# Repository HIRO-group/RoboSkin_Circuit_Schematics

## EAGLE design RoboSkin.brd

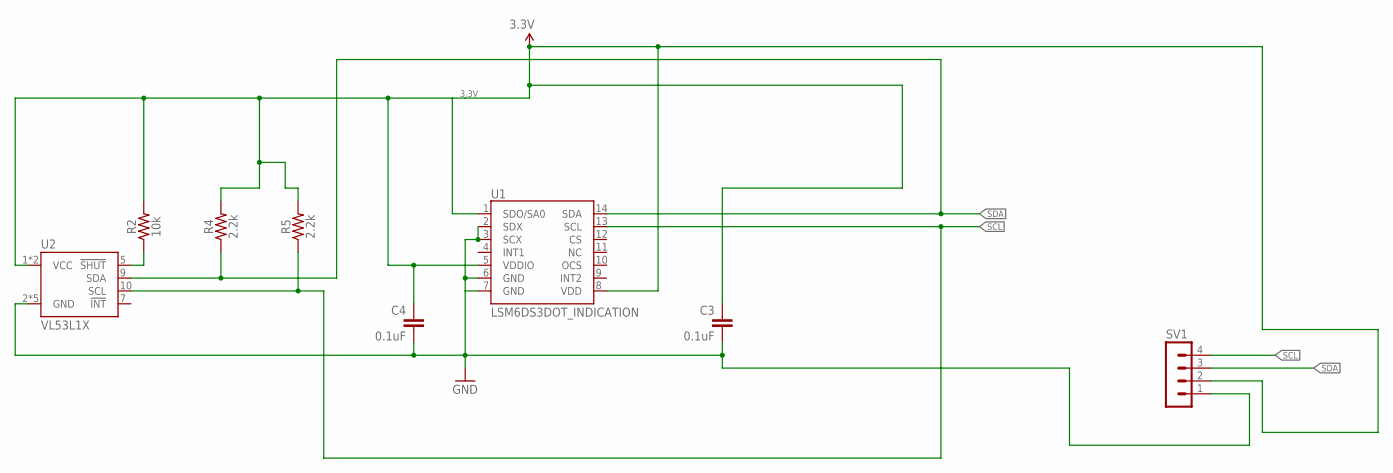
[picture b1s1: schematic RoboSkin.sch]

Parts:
C3, C4: 0.1uF; 0603-CAP
R2: 10k; 0603
R4, R5: 2.2k; 0603
SV1: MA04-1
U1: LSM6DS3DOT_INDICATION; LGA14L_DOT_INDICATOR
U2: VL53L1X

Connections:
3.3V: C3.1, C4.1, R2.2, R4.2, R5.2, SV1.2, U1.1 (SDO/SA0), U1.5 (VDDIO), U1.8 (VDD), U2.1 (VCC), U2.11 (VCC)
!SHUT: R2.1, U2.5 (!SHUT)
GND: C3.2, C4.2, SV1.1, U1.2 (SDX), U1.3 (SCX), U1.6 (GND), U1.7 (GND), U2.2 (GND), U2.3 (GND), U2.4 (GND), U2.6 (GND), U2.12 (GND)
SCL: R5.1, SV1.4, U1.13 (SCL), U2.10 (SCL)
SDA: R4.1, SV1.3, U1.14 (SDA), U2.9 (SDA)

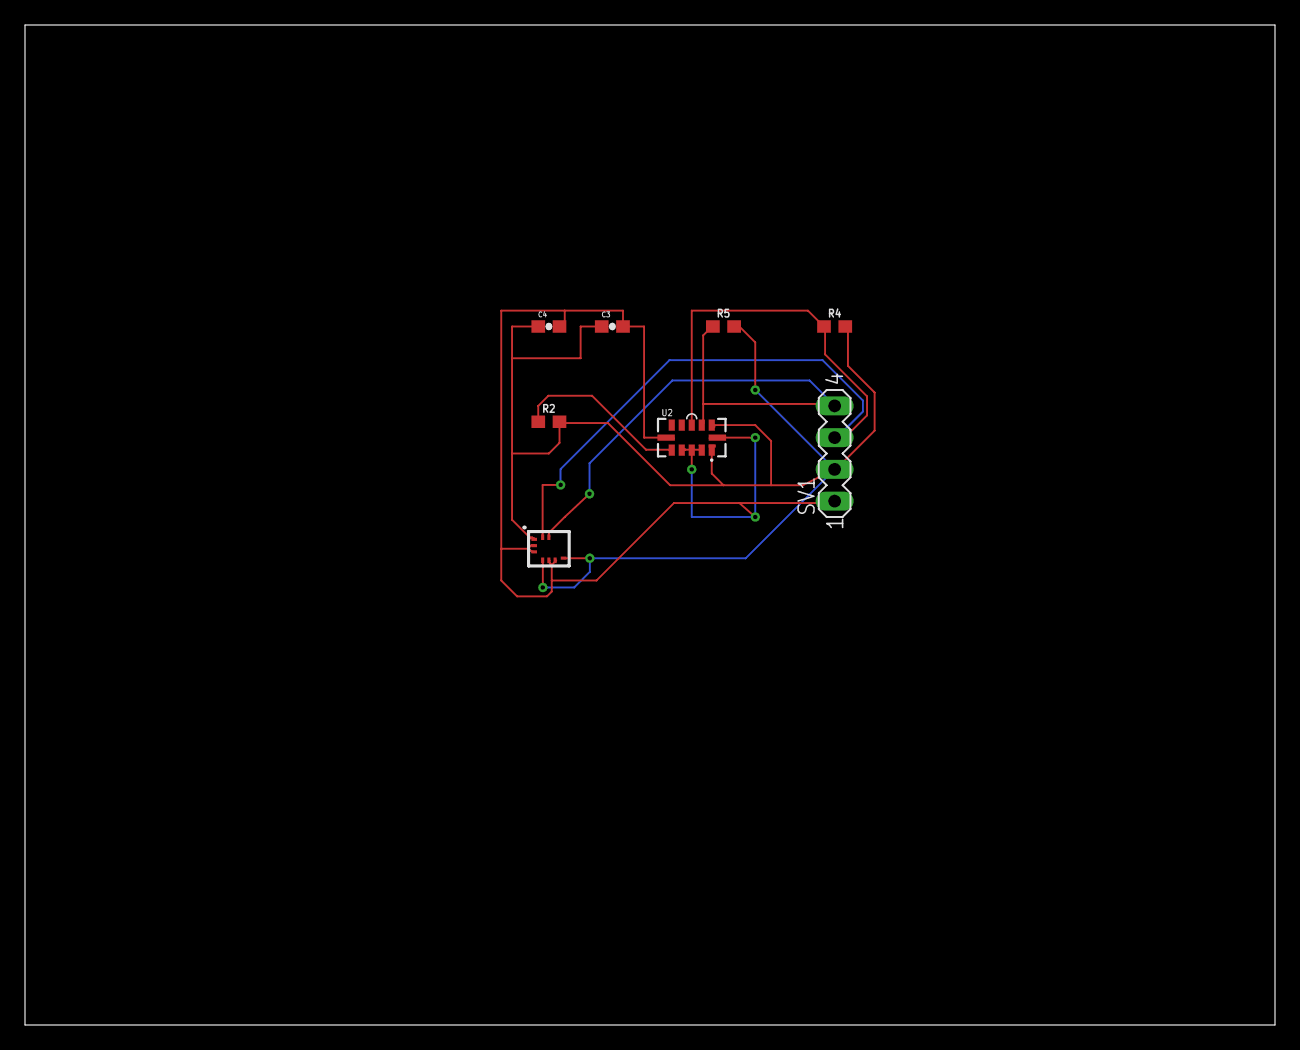
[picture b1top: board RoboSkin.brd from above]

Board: 2 copper layers, 100.0 x 80.0 mm, 8 parts (0 on the bottom side), 5 nets.

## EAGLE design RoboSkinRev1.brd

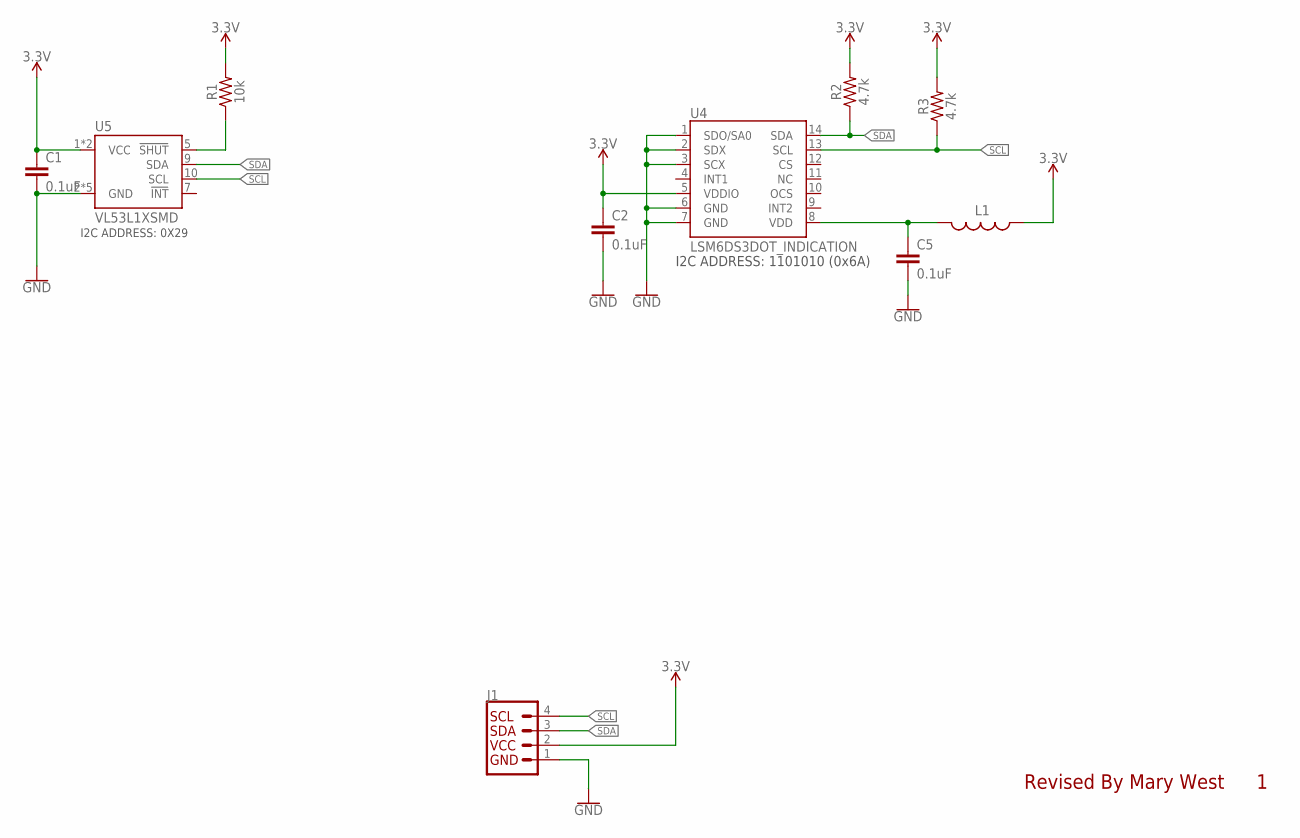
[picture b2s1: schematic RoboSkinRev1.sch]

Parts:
C1, C2, C5: 0.1uF; 0603
J1: QWIIC_CONNECTORJS-1MM; 1X04_1MM_RA
L1: RES-07859; 0603
R1: 10k; 0603
R2, R3: 4.7k; 0603
U4: LSM6DS3DOT_INDICATION; LGA14L_DOT_INDICATOR
U5: VL53L1XSMD; VL53L1X

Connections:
3.3V: C1.1, C2.1, J1.2 (VCC), L1.1, R1.2, R2.2, R3.2, U4.5 (VDDIO), U5.1 (VCC), U5.11 (VCC)
GND: C1.2, C2.2, C5.2, J1.1 (GND), U4.1 (SDO/SA0), U4.2 (SDX), U4.3 (SCX), U4.6 (GND), U4.7 (GND), U5.2 (GND), U5.3 (GND), U5.4 (GND), U5.6 (GND), U5.12 (GND)
unnamed: R1.1, U5.5 (!SHUT)
unnamed: C5.1, L1.2, U4.8 (VDD)
SCL: J1.4 (SCL), R3.1, U4.13 (SCL), U5.10 (SCL)
SDA: J1.3 (SDA), R2.1, U4.14 (SDA), U5.9 (SDA)

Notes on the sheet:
I2C ADDRESS: 1101010 (0x6A)
Revised By Mary West
I2C ADDRESS: 0X29

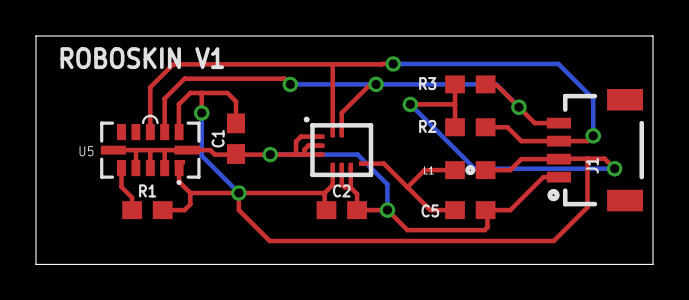
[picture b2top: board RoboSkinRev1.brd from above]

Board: 2 copper layers, 34.3 x 12.7 mm, 11 parts (1 on the bottom side), 6 nets.

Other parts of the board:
U$1: CAPTURE#PNG

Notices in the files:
parts and their libraries:
SparkFun-Capacitors: Licensing: Creative Commons ShareAlike 4.0 International - https://creativecommons.org/licenses/by-sa/4.0
